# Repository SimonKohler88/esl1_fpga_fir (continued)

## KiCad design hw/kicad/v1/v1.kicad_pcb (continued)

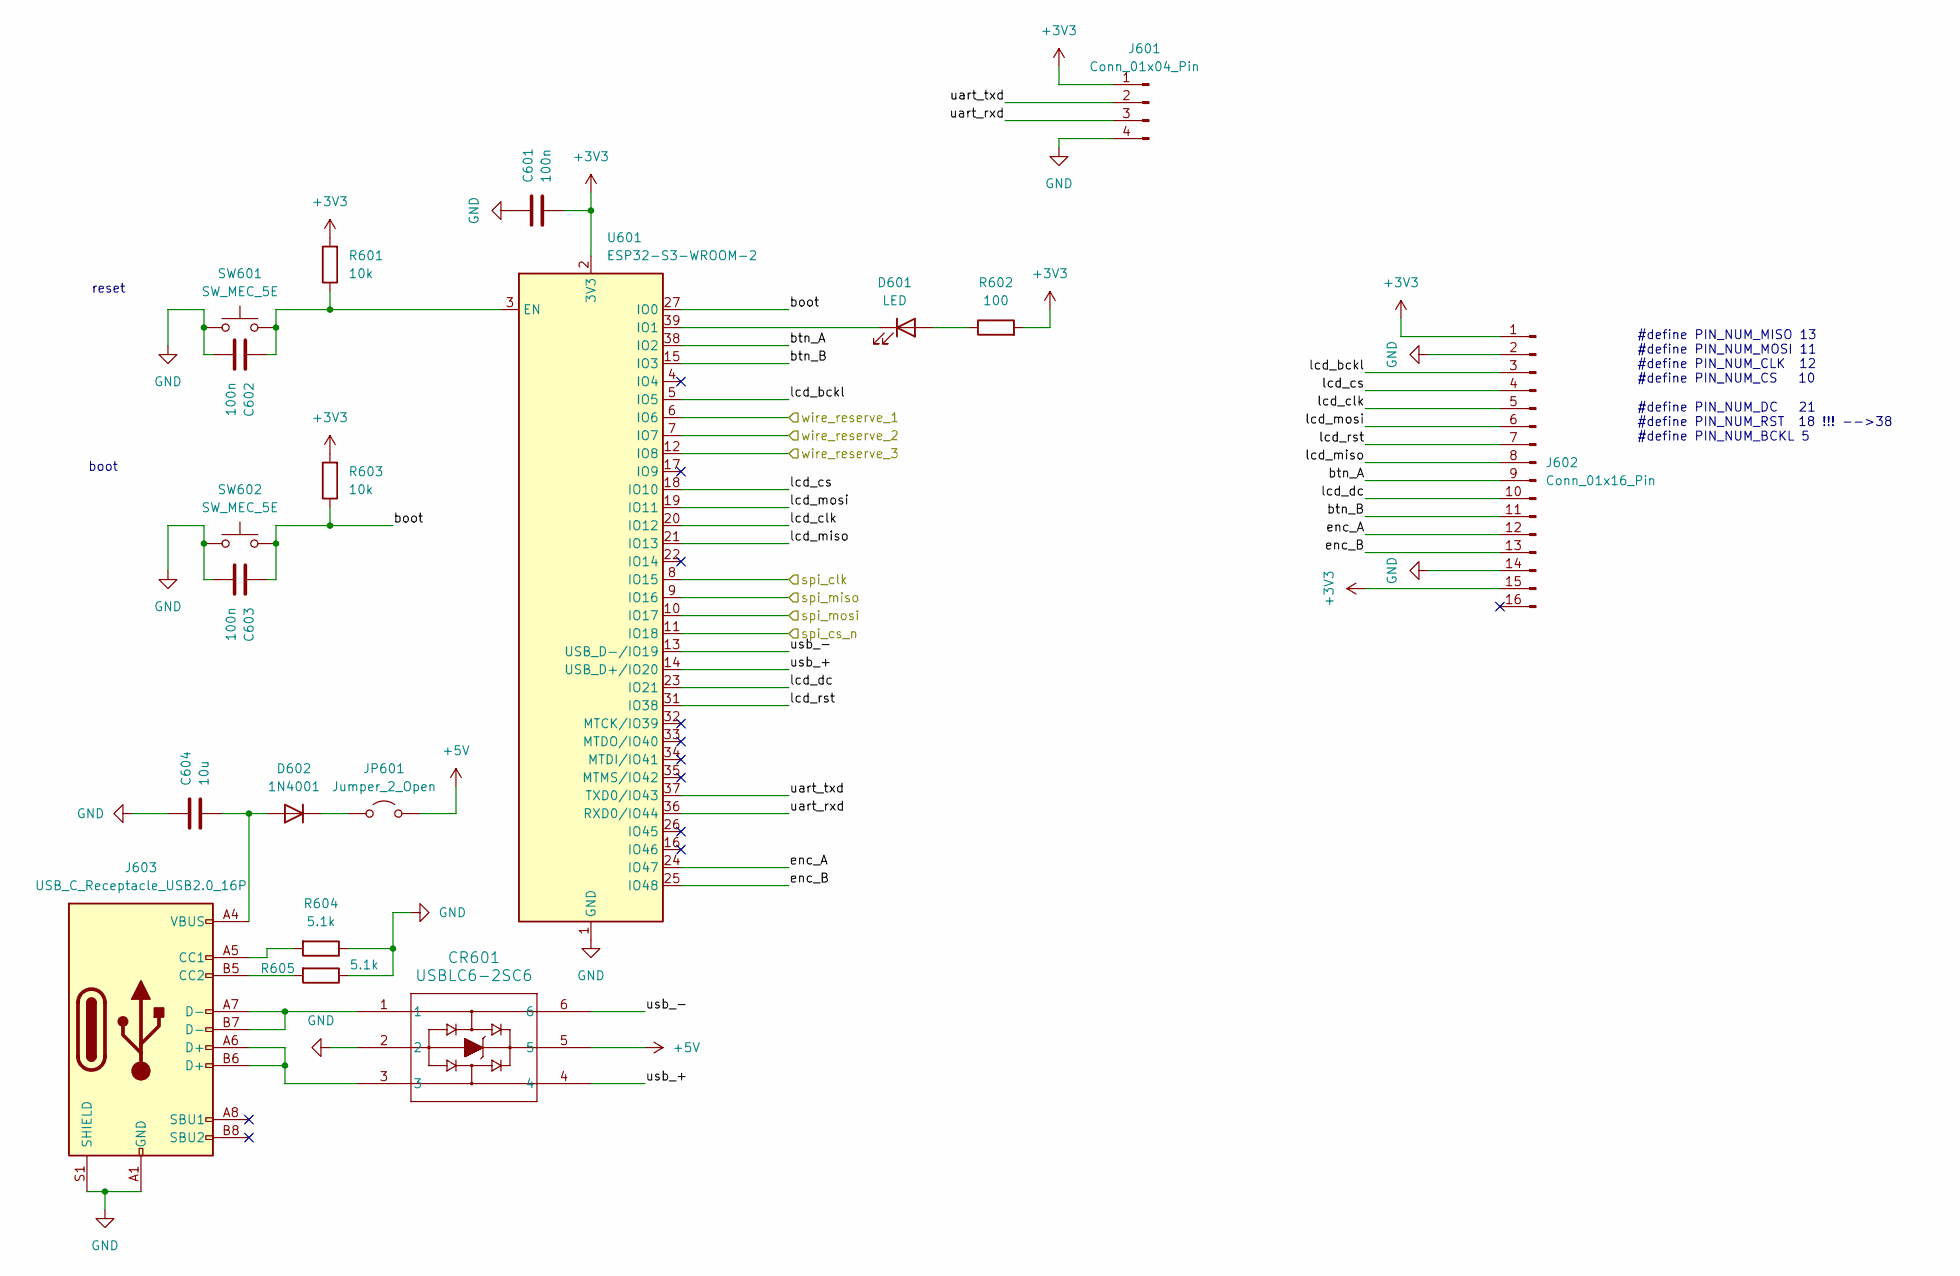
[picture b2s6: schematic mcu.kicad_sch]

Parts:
C601, C602, C603: 100n; C_1206_3216Metric_Pad1.33x1.80mm_HandSolder
C604: 10u; C_1206_3216Metric_Pad1.33x1.80mm_HandSolder
CR601: USBLC6-2SC6; SOT-23-6_Handsoldering
D601: LED; LED_1206_3216Metric_Pad1.42x1.75mm_HandSolder
D602: 1N4001; D_DO-41_SOD81_P10.16mm_Horizontal
J601: Conn_01x04_Pin; PinHeader_1x04_P2.54mm_Vertical
J602: Conn_01x16_Pin; PinHeader_2x08_P2.54mm_Vertical
J603: USB_C_Receptacle_USB2.0_16P; USB_C_Receptacle_GCT_USB4105-xx-A_16P_TopMnt_Horizontal
JP601: Jumper_2_Open; PinHeader_1x02_P2.54mm_Vertical
R601, R603: 10k; R_1206_3216Metric_Pad1.30x1.75mm_HandSolder
R602: 100; R_1206_3216Metric_Pad1.30x1.75mm_HandSolder
R604, R605: 5.1k; R_1206_3216Metric_Pad1.30x1.75mm_HandSolder
SW601, SW602: SW_MEC_5E; SW_Push_1P1T_NO_CK_KSC9xxJ
U601: ESP32-S3-WROOM-2

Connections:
+3V3: C601.2, J601.1, J602.1, J602.15, R601.2, R602.2, R603.2, U601.2 (3V3); also elsewhere on the board
+5V: CR601.5, JP601.2 (B); also elsewhere on the board
/DSV/spi_clk: U601.8 (IO15); also elsewhere on the board
/DSV/spi_cs_n: U601.11 (IO18); also elsewhere on the board
/DSV/spi_miso: U601.9 (IO16); also elsewhere on the board
/DSV/spi_mosi: U601.10 (IO17); also elsewhere on the board
/DSV/wire_reserve_1: U601.6 (IO6); also elsewhere on the board
/DSV/wire_reserve_2: U601.7 (IO7); also elsewhere on the board
/DSV/wire_reserve_3: U601.12 (IO8); also elsewhere on the board
/MCU/boot: C603.1, R603.1, SW602.2, U601.27 (IO0)
/MCU/btn_A: J602.9, U601.38 (IO2)
/MCU/btn_B: J602.11, U601.15 (IO3)
/MCU/enc_A: J602.12, U601.24 (IO47)
/MCU/enc_B: J602.13, U601.25 (IO48)
/MCU/lcd_bckl: J602.3, U601.5 (IO5)
/MCU/lcd_clk: J602.5, U601.20 (IO12)
/MCU/lcd_cs: J602.4, U601.18 (IO10)
/MCU/lcd_dc: J602.10, U601.23 (IO21)
/MCU/lcd_miso: J602.8, U601.21 (IO13)
/MCU/lcd_mosi: J602.6, U601.19 (IO11)
/MCU/lcd_rst: J602.7, U601.31 (IO38)
/MCU/uart_rxd: J601.3, U601.36 (RXD0/IO44)
/MCU/uart_txd: J601.2, U601.37 (TXD0/IO43)
/MCU/usb_+: CR601.4, U601.14 (USB_D+/IO20)
/MCU/usb_-: CR601.6, U601.13 (USB_D-/IO19)
GND: C601.1, C602.2, C603.2, C604.1, CR601.2, J601.4, J602.2, J602.14, J603.A1 (GND), J603.A12 (GND), J603.B1 (GND), J603.B12 (GND), J603.S1 (SHIELD), R604.1, R605.1, SW601.1, SW602.1, U601.1 (GND), U601.40 (GND), U601.41 (GND); also elsewhere on the board
unnamed: CR601.1, J603.A7 (D-), J603.B7 (D-)
unnamed: CR601.3, J603.A6 (D+), J603.B6 (D+)
unnamed: D601.2 (A), R602.1
unnamed: D601.1 (K), U601.39 (IO1)
unnamed: C604.2, D602.2 (A), J603.A4 (VBUS), J603.A9 (VBUS), J603.B4 (VBUS), J603.B9 (VBUS)
unnamed: D602.1 (K), JP601.1 (A)
unnamed: J603.A5 (CC1), R604.2
unnamed: J603.B5 (CC2), R605.2
unnamed: C602.1, R601.1, SW601.2, U601.3 (EN)

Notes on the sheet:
boot
reset
#define PIN_NUM_MISO 13 #define PIN_NUM_MOSI 11 #define PIN_NUM_CLK 12 #define PIN_NUM_CS 10 #define PIN_NUM_DC 21 #define PIN_NUM_RST 18 !!! -->38 #define PIN_NUM_BCKL 5

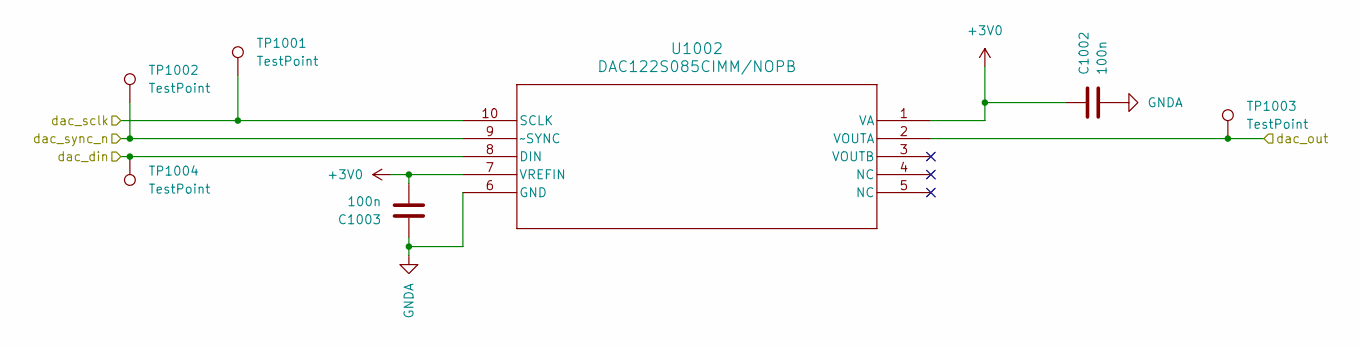
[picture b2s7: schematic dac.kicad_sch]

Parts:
C1002, C1003: 100n; C_1206_3216Metric_Pad1.33x1.80mm_HandSolder
TP1001, TP1002, TP1003, TP1004: TestPoint; TestPoint_Pad_D1.0mm
U1002: DAC122S085CIMM/NOPB; VSSOP-10_3x3mm_P0.5mm

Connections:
+3V0: C1002.1, C1003.2, U1002.1 (VA), U1002.7 (VREFIN); also elsewhere on the board
/Analog Output/DAC/dac_out: TP1003.1, U1002.2 (VOUTA); also elsewhere on the board
/Analog Output/dac_din: TP1004.1, U1002.8 (DIN); also elsewhere on the board
/Analog Output/dac_sclk: TP1001.1, U1002.10 (SCLK); also elsewhere on the board
/Analog Output/dac_sync_n: TP1002.1, U1002.9 (~SYNC); also elsewhere on the board
GND: C1002.2, C1003.1, U1002.6 (GND); also elsewhere on the board

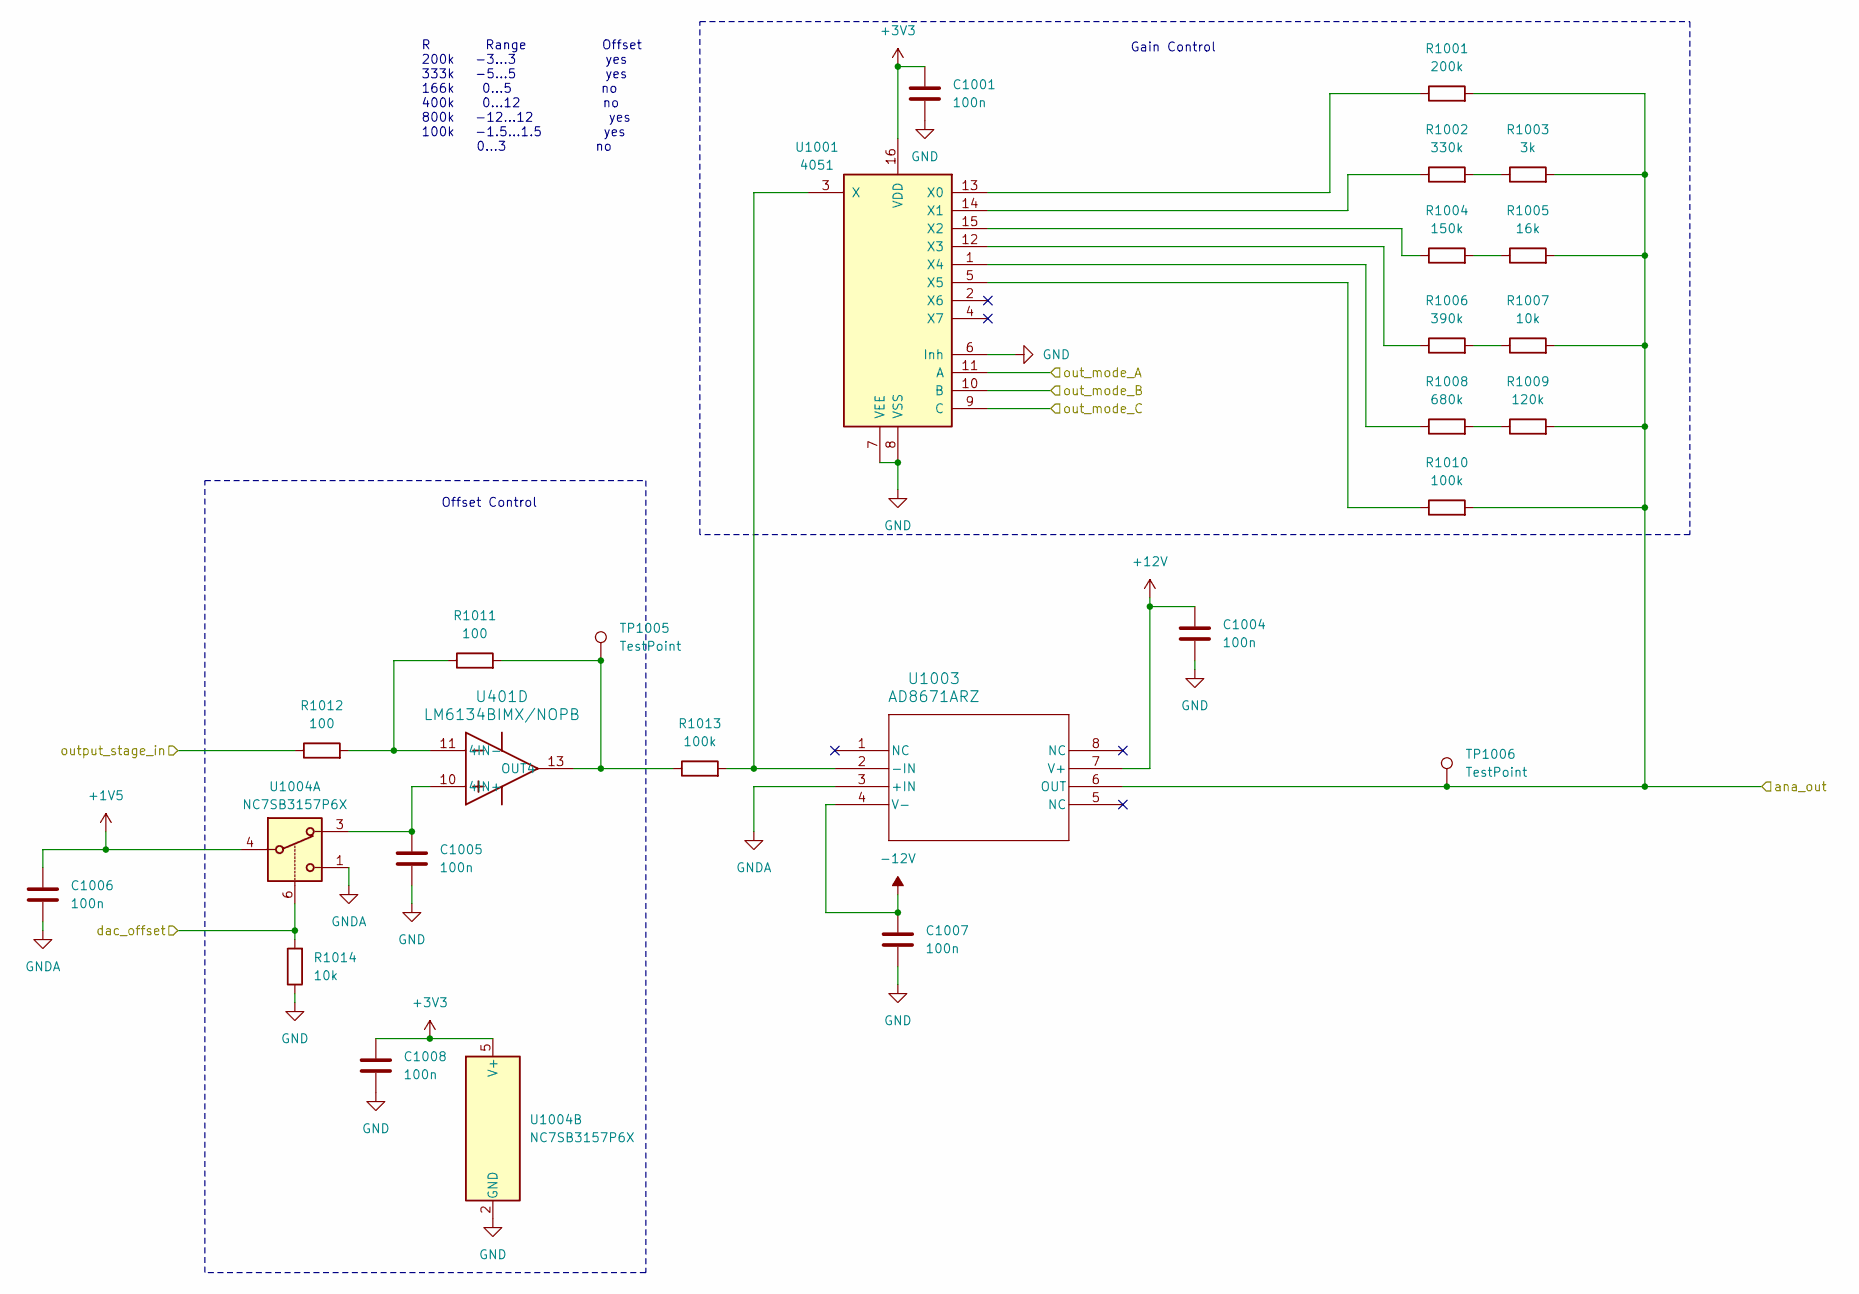
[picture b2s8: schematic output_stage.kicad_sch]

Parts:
C1001, C1004, C1005, C1007, C1008: 100n; C_1206_3216Metric_Pad1.33x1.80mm_HandSolder
C1006: 100n; C_0603_1608Metric_Pad1.08x0.95mm_HandSolder
R1001: 200k; R_1206_3216Metric_Pad1.30x1.75mm_HandSolder
R1002: 330k; R_1206_3216Metric_Pad1.30x1.75mm_HandSolder
R1003: 3k; R_1206_3216Metric_Pad1.30x1.75mm_HandSolder
R1004: 150k; R_1206_3216Metric_Pad1.30x1.75mm_HandSolder
R1005: 16k; R_1206_3216Metric_Pad1.30x1.75mm_HandSolder
R1006: 390k; R_1206_3216Metric_Pad1.30x1.75mm_HandSolder
R1007, R1014: 10k; R_1206_3216Metric_Pad1.30x1.75mm_HandSolder
R1008: 680k; R_1206_3216Metric_Pad1.30x1.75mm_HandSolder
R1009: 120k; R_1206_3216Metric_Pad1.30x1.75mm_HandSolder
R1010, R1013: 100k; R_1206_3216Metric_Pad1.30x1.75mm_HandSolder
R1011, R1012: 100; R_1206_3216Metric_Pad1.30x1.75mm_HandSolder
TP1005, TP1006: TestPoint; TestPoint_Pad_D1.0mm
U401: LM6134BIMX/NOPB; SOIC-14_3.9x8.7mm_P1.27mm
U1001: 4051; SOIC-16_3.9x9.9mm_P1.27mm
U1003: AD8671ARZ; R_8_ADI
U1004: NC7SB3157P6X; SOT-363_SC-70-6

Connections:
+1V5: C1006.1, U1004.4; also elsewhere on the board
+3V3: C1001.1, C1008.1, U1001.16 (VDD), U1004.5 (V+); also elsewhere on the board
+12V: C1004.1, U1003.7 (V+); also elsewhere on the board
-12V: C1007.1, U1003.4 (V-); also elsewhere on the board
/Analog Output/Output Stage/output_stage_in: R1012.1; also elsewhere on the board
/Analog Output/ana_out: R1001.2, R1003.2, R1005.2, R1007.2, R1009.2, R1010.2, TP1006.1, U1003.6 (OUT); also elsewhere on the board
/Analog Output/dac_offset: R1014.2, U1004.6; also elsewhere on the board
/Analog Output/out_mode_A: U1001.11 (A); also elsewhere on the board
/Analog Output/out_mode_B: U1001.10 (B); also elsewhere on the board
/Analog Output/out_mode_C: U1001.9 (C); also elsewhere on the board
GND: C1001.2, C1004.2, C1005.2, C1006.2, C1007.2, C1008.2, R1014.1, U1001.6 (Inh), U1001.7 (VEE), U1001.8 (VSS), U1003.3 (+IN), U1004.1, U1004.2 (GND); also elsewhere on the board
unnamed: R1002.2, R1003.1
unnamed: R1004.2, R1005.1
unnamed: R1006.2, R1007.1
unnamed: R1008.2, R1009.1
unnamed: C1005.1, U401.10 (4IN+), U1004.3
unnamed: R1011.1, R1012.2, U401.11 (4IN-)
unnamed: R1011.2, R1013.1, TP1005.1, U401.13 (OUT4)
unnamed: R1001.1, U1001.13 (X0)
unnamed: R1002.1, U1001.14 (X1)
unnamed: R1004.1, U1001.15 (X2)
unnamed: R1006.1, U1001.12 (X3)
unnamed: R1008.1, U1001.1 (X4)
unnamed: R1010.1, U1001.5 (X5)
unnamed: R1013.2, U1001.3 (X), U1003.2 (-IN)

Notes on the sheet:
R Range Offset 200k -3...3 yes 333k -5...5 yes 166k 0...5 no 400k 0...12 no 800k -12...12 yes 100k -1.5...1.5 yes 0...3 no
Offset Control
Gain Control

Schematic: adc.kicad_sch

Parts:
C901: 100n; C_1206_3216Metric_Pad1.33x1.80mm_HandSolder
C902: 3.3u; C_1206_3216Metric_Pad1.33x1.80mm_HandSolder
C903: 470p; C_0603_1608Metric_Pad1.08x0.95mm_HandSolder
D901, D902: BZV55B3V3; D_MiniMELF
R901: 100; R_1206_3216Metric_Pad1.30x1.75mm_HandSolder
TP901, TP902, TP903, TP904: TestPoint; TestPoint_Pad_D1.0mm
U901: TLV9022DR; SOIC-8_3.9x4.9mm_P1.27mm
U902: ADS7883SBDBVT; SOT-23-6_Handsoldering

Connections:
+3V0: C902.2, U902.1 (VDD); also elsewhere on the board
+3V3: C901.1, D901.1 (K), U901.3 (IN1+), U901.8 (VCC); also elsewhere on the board
/DSV/adc_cs_n: TP903.1, U902.6 (CS_N); also elsewhere on the board
/DSV/adc_sclk: TP901.1, U902.4 (SCLK); also elsewhere on the board
/DSV/adc_sdo: TP902.1, U902.5 (SDO); also elsewhere on the board
/DSV/clip_high_out: U901.1 (OUT1); also elsewhere on the board
/DSV/clip_low_out: U901.7 (OUT2); also elsewhere on the board
/analog Input/ADC/adc_in: R901.1; also elsewhere on the board
GND: C901.2, C902.1, C903.2, D902.2 (A), U901.4 (GND), U901.6 (IN2-), U902.2 (GND); also elsewhere on the board
unnamed: C903.1, D901.2 (A), D902.1 (K), R901.2, TP904.1, U901.2 (IN1-), U901.5 (IN2+), U902.3 (VIN)

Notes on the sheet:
ADC protection
clipping detection

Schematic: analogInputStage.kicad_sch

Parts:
C701, C702, C703, C704, C706: 100n; C_1206_3216Metric_Pad1.33x1.80mm_HandSolder
C705: 100n; C_0603_1608Metric_Pad1.08x0.95mm_HandSolder
D701, D702: BZV55B12; D_MiniMELF
R701: 47k; R_1206_3216Metric_Pad1.30x1.75mm_HandSolder
R702, R704, R709: 2k7; R_1206_3216Metric_Pad1.30x1.75mm_HandSolder
R703: 27k; R_1206_3216Metric_Pad1.30x1.75mm_HandSolder
R705: 56k; R_1206_3216Metric_Pad1.30x1.75mm_HandSolder
R706: 3k6; R_1206_3216Metric_Pad1.30x1.75mm_HandSolder
R707: 160; R_1206_3216Metric_Pad1.30x1.75mm_HandSolder
R708: 22k; R_1206_3216Metric_Pad1.30x1.75mm_HandSolder
R710: 11k; R_1206_3216Metric_Pad1.30x1.75mm_HandSolder
R711: 240; R_1206_3216Metric_Pad1.30x1.75mm_HandSolder
R712: 91k; R_1206_3216Metric_Pad1.30x1.75mm_HandSolder
R713: 8k2; R_1206_3216Metric_Pad1.30x1.75mm_HandSolder
R714: 560; R_1206_3216Metric_Pad1.30x1.75mm_HandSolder
R715, R717: 100; R_1206_3216Metric_Pad1.30x1.75mm_HandSolder
R716: 100k; R_1206_3216Metric_Pad1.30x1.75mm_HandSolder
R718: 10k; R_1206_3216Metric_Pad1.30x1.75mm_HandSolder
TP701, TP702, TP703: TestPoint; TestPoint_Pad_D1.0mm
U301: LM6134BIMX/NOPB; SOIC-14_3.9x8.7mm_P1.27mm
U701: 4051; SOIC-16_3.9x9.9mm_P1.27mm
U702: NC7SB3157P6X; SOT-363_SC-70-6
U703: AD8671ARZ; R_8_ADI

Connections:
+1V5: C705.1, U702.4; also elsewhere on the board
+3V3: C701.1, C702.1, U701.16 (VDD), U702.5 (V+); also elsewhere on the board
+12V: C703.1, D701.1 (K), U703.7 (V+); also elsewhere on the board
-12V: C706.1, D702.2 (A), U703.4 (V-); also elsewhere on the board
/DSV/adc_offset: R718.2, U702.6; also elsewhere on the board
/DSV/inp_mode_A: U701.11 (A); also elsewhere on the board
/DSV/inp_mode_B: U701.10 (B); also elsewhere on the board
/DSV/inp_mode_C: U701.9 (C); also elsewhere on the board
/analog Input/ana_in: D701.2 (A), D702.1 (K), R716.1, TP701.1; also elsewhere on the board
/analog Input/analog input stage/input_stage_out: R715.2, TP703.1, U301.2 (OUT1); also elsewhere on the board
GND: C701.2, C702.2, C703.2, C704.2, C705.2, C706.2, R718.1, U701.6 (Inh), U701.7 (VEE), U701.8 (VSS), U702.1, U702.2 (GND), U703.3 (+IN); also elsewhere on the board
unnamed: R701.2, R702.1
unnamed: R703.2, R704.1
unnamed: R705.2, R706.1
unnamed: R706.2, R707.1
unnamed: R708.2, R709.1
unnamed: R710.2, R711.1
unnamed: R712.2, R713.1
unnamed: R713.2, R714.1
unnamed: C704.1, U301.5 (1IN+), U702.3
unnamed: R715.1, R717.2, U301.4 (1IN-)
unnamed: R701.1, U701.13 (X0)
unnamed: R703.1, U701.14 (X1)
unnamed: R705.1, U701.15 (X2)
unnamed: R708.1, U701.12 (X3)
unnamed: R710.1, U701.1 (X4)
unnamed: R712.1, U701.5 (X5)
unnamed: R716.2, U701.3 (X), U703.2 (-IN)
unnamed: R702.2, R704.2, R707.2, R709.2, R711.2, R714.2, R717.1, TP702.1, U703.6 (OUT)

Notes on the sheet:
R Range Offset 50k0 -3...3 yes 30k0 -5...5 yes 60k 0...5 no 25k 0...12 no 12k5 -12...12 yes 100k -1.5...1.5 yes 0...3 no
Gain Control
Offset Control

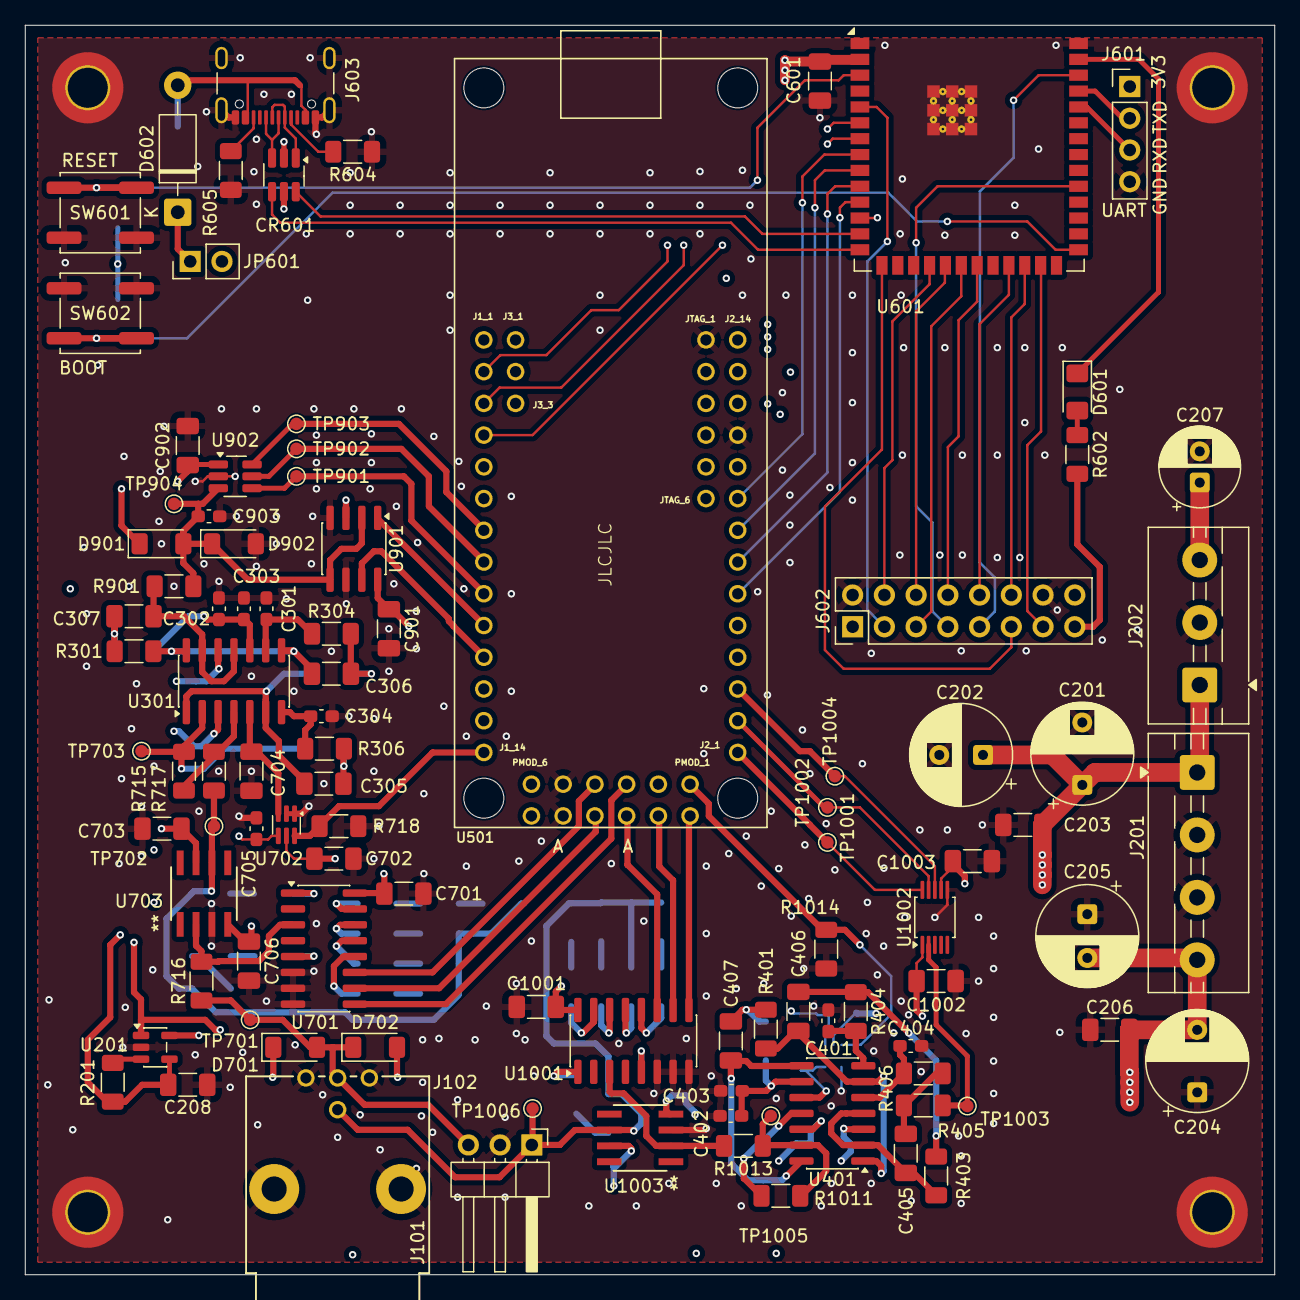
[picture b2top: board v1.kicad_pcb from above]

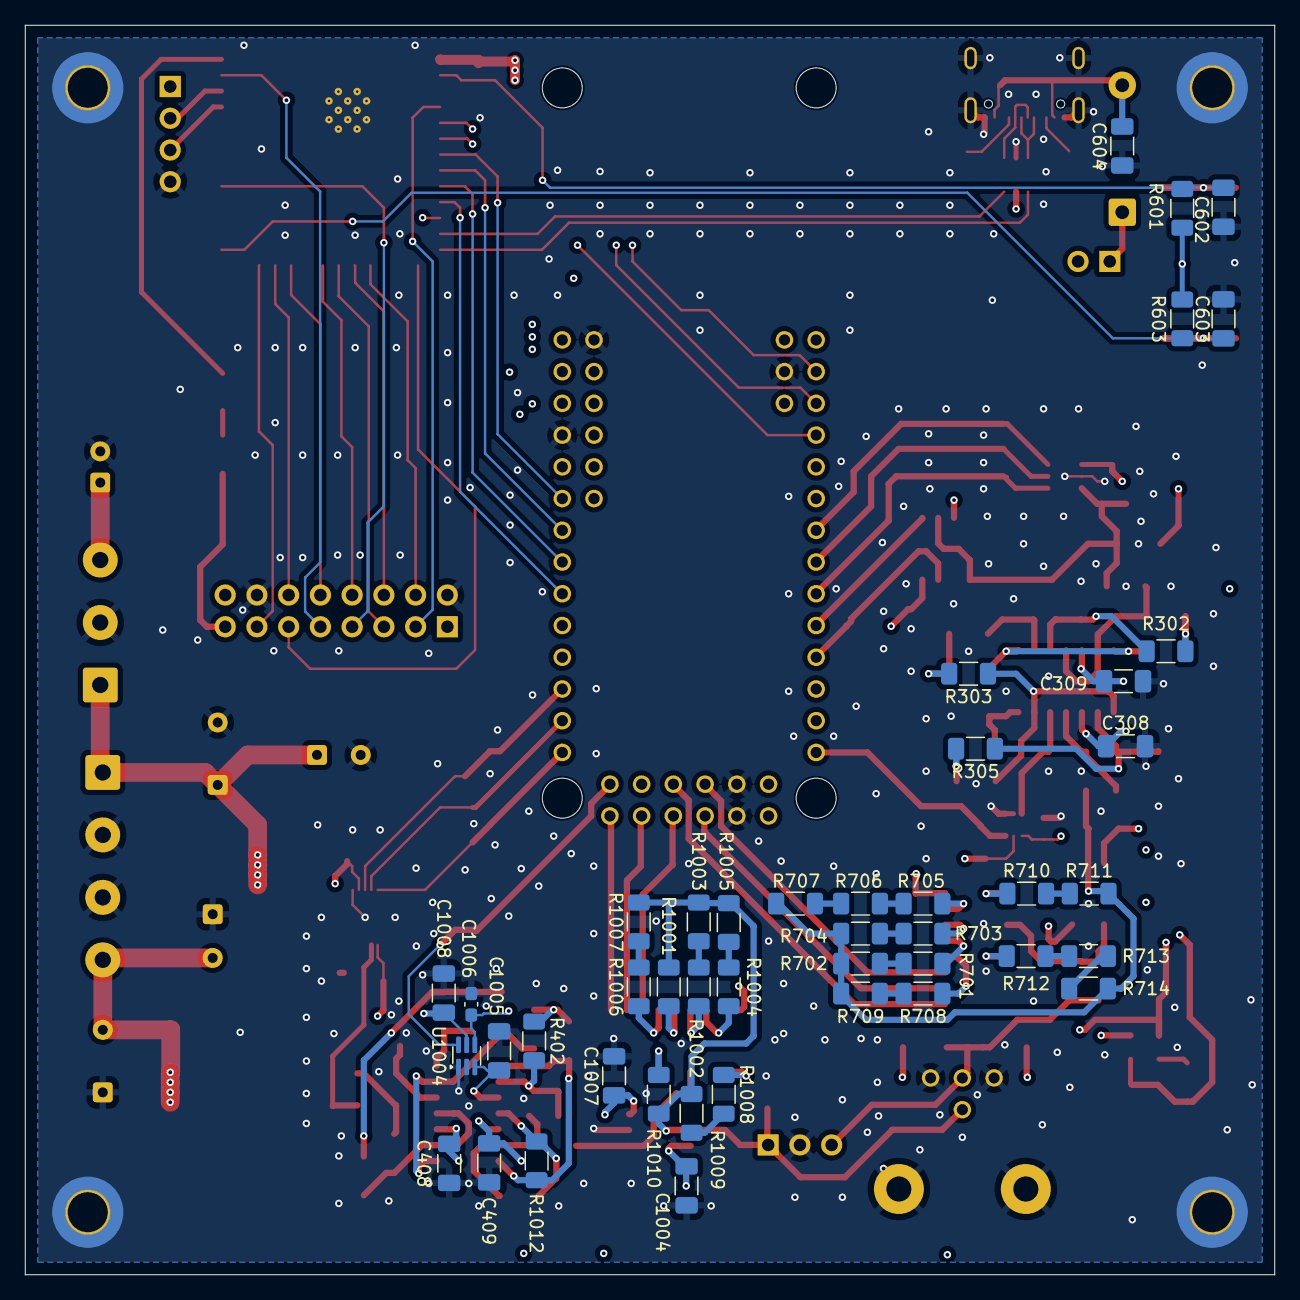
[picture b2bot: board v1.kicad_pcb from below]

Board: 4 copper layers, 100.0 x 100.0 mm, 146 parts (44 on the bottom side), 111 nets.

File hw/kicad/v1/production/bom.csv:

Designator,Footprint,Quantity,Value,LCSC Part #
"C1001, C1002, C1003, C1004, C1005, C1007, C1008, C203, C206, C208, C308, C309, C408, C409, C601, C602, C603, C701, C702, C703, C704, C706, C901",1206,23,100n,
"C1006, C705",0603,2,100n,
"C201, C204",CP_Radial_D8.0mm_P5.00mm,2,680u,
"C202, C205",CP_Radial_D8.0mm_P3.50mm,2,100u,
C207,CP_Radial_D6.3mm_P2.50mm,1,10u,
"C301, C302, C401, C402, C903",0603,5,470p,
"C303, C403",0603,2,330p,
"C304, C404",0603,2,68p,
"C305, C306, C307, C405, C406, C407",1206,6,1n,
C604,1206,1,10u,
C902,1206,1,3.3u,
CR601,SOT-23-6_Handsoldering,1,USBLC6-2SC6,
D601,1206,1,LED,
D602,D_DO-41_SOD81_P10.16mm_Horizontal,1,1N4001,
"D701, D702",D_MiniMELF,2,BZV55B12,
"D901, D902",D_MiniMELF,2,BZV55B3V3,
J101,PinHeader_1x03_P2.54mm_Horizontal,1,Conn_01x03_Pin,
J102,CONN_6575_AMP,1,031-6575,
J201,TerminalBlock_MaiXu_MX126-5.0-04P_1x04_P5.00mm,1,Screw_Terminal_01x04,
J202,TerminalBlock_MaiXu_MX126-5.0-03P_1x03_P5.00mm,1,Screw_Terminal_01x03,
J601,PinHeader_1x04_P2.54mm_Vertical,1,Conn_01x04_Pin,
J602,PinHeader_2x08_P2.54mm_Vertical,1,Conn_01x16_Pin,
J603,USB_C_Receptacle_GCT_USB4105-xx-A_16P_TopMnt_Horizontal,1,USB_C_Receptacle_USB2.0_16P,
JP601,PinHeader_1x02_P2.54mm_Vertical,1,Jumper_2_Open,
R1001,1206,1,200k,
R1002,1206,1,330k,
R1003,1206,1,3k,
R1004,1206,1,150k,
R1005,1206,1,16k,
R1006,1206,1,390k,
"R1007, R1014, R201, R601, R603, R718",1206,6,10k,
R1008,1206,1,680k,
R1009,1206,1,120k,
"R1010, R1013, R716",1206,3,100k,
"R1011, R1012, R602, R715, R717, R901",1206,6,100,
"R301, R401",1206,2,120,
"R302, R402, R711",1206,3,240,
"R303, R403, R707",1206,3,160,
"R304, R404",1206,2,360,
"R305, R405",1206,2,470,
"R306, R406",1206,2,820,
"R604, R605",1206,2,5.1k,
R701,1206,1,47k,
"R702, R704, R709",1206,3,2k7,
R703,1206,1,27k,
R705,1206,1,56k,
R706,1206,1,3k6,
R708,1206,1,22k,
R710,1206,1,11k,
R712,1206,1,91k,
R713,1206,1,8k2,
R714,1206,1,560,
"SW601, SW602",SW_Push_1P1T_NO_CK_KSC9xxJ,2,SW_MEC_5E,
"TP1001, TP1002, TP1003, TP1004, TP1005, TP1006, TP701, TP702, TP703, TP901, TP902, TP903, TP904",TestPoint_Pad_D1.0mm,13,TestPoint,
"U1001, U701",SOIC-16_3.9x9.9mm_P1.27mm,2,4051,
U1002,VSSOP-10_3x3mm_P0.5mm,1,DAC122S085CIMM/NOPB,
"U1003, U703",R_8_ADI,2,AD8671ARZ,
"U1004, U702",SOT-363_SC-70-6,2,NC7SB3157P6X,
U201,SOT-23-5,1,REF2030,
"U301, U401",SOIC-14_3.9x8.7mm_P1.27mm,2,LM6134BIMX/NOPB,
U501,MAX1000,1,MAX1000,
U601,ESP32-S3-WROOM-2,1,ESP32-S3-WROOM-2,
U901,SOIC-8_3.9x4.9mm_P1.27mm,1,TLV9022DR,
U902,SOT-23-6_Handsoldering,1,ADS7883SBDBVT,

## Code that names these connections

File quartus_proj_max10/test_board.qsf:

# -------------------------------------------------------------------------- #
#
# Copyright (C) 2024  Intel Corporation. All rights reserved.
# Your use of Intel Corporation's design tools, logic functions 
# and other software and tools, and any partner logic 
# functions, and any output files from any of the foregoing 
# (including device programming or simulation files), and any 
# associated documentation or information are expressly subject 
# to the terms and conditions of the Intel Program License 
# Subscription Agreement, the Intel Quartus Prime License Agreement,
# the Intel FPGA IP License Agreement, or other applicable license
# agreement, including, without limitation, that your use is for
# the sole purpose of programming logic devices manufactured by
# Intel and sold by Intel or its authorized distributors.  Please
# refer to the applicable agreement for further details, at
# https://fpgasoftware.intel.com/eula.
#
# -------------------------------------------------------------------------- #
#
# Quartus Prime
# Version 23.1std.1 Build 993 05/14/2024 SC Lite Edition
# Date created = 09:23:21  July 30, 2025
#
# -------------------------------------------------------------------------- #
#
# Notes:
#
# 1) The default values for assignments are stored in the file:
#		test_board_assignment_defaults.qdf
#    If this file doesn't exist, see file:
#		assignment_defaults.qdf
#
# 2) Intel recommends that you do not modify this file. This
#    file is updated automatically by the Quartus Prime software
#    and any changes you make may be lost or overwritten.
#
# -------------------------------------------------------------------------- #


set_global_assignment -name FAMILY "MAX 10"
set_global_assignment -name DEVICE 10M08SAU169C8G
set_global_assignment -name TOP_LEVEL_ENTITY test_board
set_global_assignment -name ORIGINAL_QUARTUS_VERSION 18.1.0
set_global_assignment -name PROJECT_CREATION_TIME_DATE "11:47:22  MARCH 18, 2019"
set_global_assignment -name LAST_QUARTUS_VERSION "20.1.1 Lite Edition"
set_global_assignment -name PROJECT_OUTPUT_DIRECTORY output_files
set_global_assignment -name DEVICE_FILTER_PACKAGE UFBGA
set_global_assignment -name ERROR_CHECK_FREQUENCY_DIVISOR 256
set_global_assignment -name ENABLE_OCT_DONE OFF
set_global_assignment -name USE_CONFIGURATION_DEVICE OFF
set_global_assignment -name CRC_ERROR_OPEN_DRAIN OFF
set_global_assignment -name STRATIX_DEVICE_IO_STANDARD "3.3-V LVTTL"
set_global_assignment -name PROJECT_IP_REGENERATION_POLICY ALWAYS_REGENERATE_IP
set_global_assignment -name POWER_PRESET_COOLING_SOLUTION "23 MM HEAT SINK WITH 200 LFPM AIRFLOW"
set_global_assignment -name POWER_BOARD_THERMAL_MODEL "NONE (CONSERVATIVE)"
set_global_assignment -name FLOW_ENABLE_POWER_ANALYZER ON
set_global_assignment -name POWER_DEFAULT_INPUT_IO_TOGGLE_RATE "12.5 %"
set_global_assignment -name EXTERNAL_FLASH_FALLBACK_ADDRESS 00000000
set_global_assignment -name INTERNAL_FLASH_UPDATE_MODE "SINGLE IMAGE WITH ERAM"
set_global_assignment -name ENABLE_DEVICE_WIDE_RESET OFF
set_global_assignment -name ENABLE_CONFIGURATION_PINS OFF
set_global_assignment -name PARTITION_NETLIST_TYPE SOURCE -section_id Top
set_global_assignment -name PARTITION_FITTER_PRESERVATION_LEVEL PLACEMENT_AND_ROUTING -section_id Top
set_global_assignment -name PARTITION_COLOR 16764057 -section_id Top
set_global_assignment -name OUTPUT_IO_TIMING_NEAR_END_VMEAS "HALF VCCIO" -rise
set_global_assignment -name OUTPUT_IO_TIMING_NEAR_END_VMEAS "HALF VCCIO" -fall
set_global_assignment -name OUTPUT_IO_TIMING_FAR_END_VMEAS "HALF SIGNAL SWING" -rise
set_global_assignment -name OUTPUT_IO_TIMING_FAR_END_VMEAS "HALF SIGNAL SWING" -fall
set_location_assignment PIN_A12 -to DQ[15]
set_location_assignment PIN_B13 -to DQ[14]
set_location_assignment PIN_B12 -to DQ[13]
set_location_assignment PIN_C12 -to DQ[12]
set_location_assignment PIN_D12 -to DQ[11]
set_location_assignment PIN_E13 -to DQ[10]
set_location_assignment PIN_E12 -to DQ[9]
set_location_assignment PIN_F13 -to DQ[8]
set_location_assignment PIN_F8 -to DQ[7]
set_location_assignment PIN_G9 -to DQ[6]
set_location_assignment PIN_D9 -to DQ[5]
set_location_assignment PIN_E10 -to DQ[4]
set_location_assignment PIN_F9 -to DQ[3]
set_location_assignment PIN_F10 -to DQ[2]
set_location_assignment PIN_G10 -to DQ[1]
set_location_assignment PIN_D11 -to DQ[0]
set_location_assignment PIN_M10 -to A[11]
set_location_assignment PIN_N4 -to A[10]
set_location_assignment PIN_N8 -to A[9]
set_location_assignment PIN_M13 -to A[8]
set_location_assignment PIN_L10 -to A[7]
set_location_assignment PIN_N9 -to A[6]
set_location_assignment PIN_M11 -to A[5]
set_location_assignment PIN_N10 -to A[4]
set_location_assignment PIN_J8 -to A[3]
set_location_assignment PIN_N5 -to A[2]
set_location_assignment PIN_M5 -to A[1]
set_location_assignment PIN_K6 -to A[0]
set_location_assignment PIN_H6 -to CLK12M
set_location_assignment PIN_F12 -to DQM[1]
set_location_assignment PIN_E9 -to DQM[0]
set_location_assignment PIN_K8 -to BA[1]
set_location_assignment PIN_N6 -to BA[0]
set_location_assignment PIN_M7 -to RAS
set_location_assignment PIN_E7 -to RESET
set_location_assignment PIN_M9 -to CLK
set_location_assignment PIN_M8 -to CKE
set_location_assignment PIN_N7 -to CAS
set_location_assignment PIN_K7 -to WE
set_location_assignment PIN_M4 -to CS
set_location_assignment PIN_E6 -to USER_BTN
set_location_assignment PIN_J6 -to SEN_SPC
set_location_assignment PIN_K5 -to SEN_SDO
set_location_assignment PIN_J7 -to SEN_SDI
set_location_assignment PIN_L5 -to SEN_CS
set_location_assignment PIN_B2 -to F_DO
set_location_assignment PIN_A2 -to F_DI
set_location_assignment PIN_B3 -to F_CS
set_location_assignment PIN_A3 -to F_CLK
set_location_assignment PIN_A4 -to BDBUS0
set_location_assignment PIN_B4 -to BDBUS1
set_location_assignment PIN_A8 -to LED0
set_location_assignment PIN_A9 -to LED1
set_location_assignment PIN_A11 -to LED2
set_location_assignment PIN_A10 -to LED3
set_location_assignment PIN_B10 -to LED4
set_location_assignment PIN_C9 -to LED5
set_location_assignment PIN_C10 -to LED6
set_location_assignment PIN_D8 -to LED7
set_location_assignment PIN_C4 -to NSTATUS
set_location_assignment PIN_B9 -to DEVCLRn
set_location_assignment PIN_M3 -to DAC_OFFSET
set_location_assignment PIN_F1 -to ADC_SPI_CS_N
set_location_assignment PIN_J2 -to ADC_OFFSET
set_location_assignment PIN_K10 -to CLIP_H
set_location_assignment PIN_H5 -to CLIP_L
set_global_assignment -name MIN_CORE_JUNCTION_TEMP 0
set_global_assignment -name MAX_CORE_JUNCTION_TEMP 85
set_location_assignment PIN_M1 -to IN_MUX[0]
set_location_assignment PIN_M2 -to IN_MUX[2]
set_location_assignment PIN_K1 -to IN_MUX[1]
set_location_assignment PIN_K2 -to OUT_MUX[0]
set_location_assignment PIN_N2 -to OUT_MUX[1]
set_location_assignment PIN_N3 -to OUT_MUX[2]
set_location_assignment PIN_E4 -to ADC_SPI_DATA_IN
set_location_assignment PIN_H8 -to ADC_SPI_CLK
set_location_assignment PIN_L12 -to DAC_SPI_CLK
set_location_assignment PIN_J12 -to DAC_SPI_CS_N
set_location_assignment PIN_J13 -to DAC_SPI_DATA
set_location_assignment PIN_G12 -to SPI_CLK
set_location_assignment PIN_J10 -to SPI_CS_N
set_location_assignment PIN_H13 -to SPI_MISO
set_location_assignment PIN_H10 -to SPI_MOSI
set_global_assignment -name VHDL_INPUT_VERSION VHDL_2008
set_global_assignment -name VHDL_SHOW_LMF_MAPPING_MESSAGES OFF
set_location_assignment PIN_E1 -to RESERVE_1
set_location_assignment PIN_C2 -to RESERVE_2
set_location_assignment PIN_C1 -to RESERVE_3
set_global_assignment -name VHDL_FILE hdl/BUS_BYPASS_MUX/BUS_BYPASS_MUX.vhdl
set_global_assignment -name VHDL_FILE hdl/MCU_SPI/spi_reg_bank.vhdl
set_global_assignment -name VHDL_FILE hdl/MCU_SPI/spi_protocol.vhdl
set_global_assignment -name VHDL_FILE hdl/MCU_SPI/spi_phy.vhdl
set_global_assignment -name VHDL_FILE hdl/MCU_SPI/spi_cmd_package.vhdl
set_global_assignment -name VHDL_FILE hdl/MCU_SPI/MCU_SPI.vhdl
set_global_assignment -name VHDL_FILE hdl/DAC_SPI/DAC_SPI.vhdl
set_global_assignment -name VHDL_FILE hdl/FIR/fir_types.vhdl
set_global_assignment -name VHDL_FILE hdl/FIR/fir_filter.vhdl
set_global_assignment -name VHDL_FILE hdl/shift_reg_seq.vhd
set_global_assignment -name VHDL_FILE hdl/pwm_seq.vhd
set_global_assignment -name VHDL_FILE hdl/knightrider.vhd
set_global_assignment -name VHDL_FILE hdl/control_mux.vhd
set_global_assignment -name VHDL_FILE hdl/case_state_seq.vhd
set_global_assignment -name QIP_FILE ddrclk.qip
set_global_assignment -name SDC_FILE test_board.out.sdc
set_global_assignment -name BDF_FILE test_board.bdf
set_global_assignment -name QIP_FILE ip/pll_megafunc/pll.qip
set_global_assignment -name VHDL_FILE "d:\\GitHub\\esl1_fpga_fir\\quartus_proj_max10\\hdl\\ADC_SPI\\ADC_SPI.vhdl"
set_global_assignment -name VHDL_FILE "d:\\GitHub\\esl1_fpga_fir\\quartus_proj_max10\\hdl\\FIR\\fir_filter_tb.vhdl"
set_instance_assignment -name PARTITION_HIERARCHY root_partition -to | -section_id Top

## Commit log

2025-11-02 Codec Files Pichler
    Codec Files Pichler
2025-11-02 base project and nios for uart
2025-11-02 working nios with uart over jtag, leds over AV MM
2025-11-09 timer isr, jtag isr, console working wy better
2025-11-09 working with jtag_uart
2025-11-09 Erster Entwurf FIR Filter Thomas
2025-11-09 we leave it at jtag_uart
2025-11-09 CODEC related files and wrapper added
    CODEC related files provided by Prof. Pichler:
    codec_i2c_config.vhd, codec_i2c_ctrl.vhd, codec_i2c_top_struct.vhd, codec_if.vhd, ime_vga_audio_pll.vhd and ime_vga_audio_pll_002.v.
    Wrapper (Avalon compatible) and Testbench for our Project:
    codec_top.vhd, codec_top_tb_vhd
2025-11-09 implemented IOS for Audio, interface to fir filter
2025-11-09 Erstelle cmake um in Clion automatisch die Testbenches zu erstellen und zu simulieren.
2025-11-09 preload a standard set of filter coefficients at startup
2025-11-10 CMakeLists.txt verbessert, dass gtkwave gleich nach der Simulation startet
2025-11-10 compile in Const register for preload FIR Koeff
2025-11-10 Now with 50MHz Avalon Streaming Handshake
    Now with 50MHz Avalon Streaming Handshake
2025-11-10 Umsetzung Filter zum Zweiten
2025-11-10 Now with 50MHz Avalon Streaming Handshake
2025-11-10 interface prog
2025-11-11 fixed Address issue
2025-11-11 switch to normal uart
2025-11-11 change to use normal uart
2025-11-11 REALLY corrected Address issue
2025-11-17 Bilder Init für Dok
2025-11-17 Doku: Jupyter
2025-11-17 Added filter computation and write
    The 64 filter coefficients can be computed and written to the FPGA by defining the cutoff frequency(s) and filter type.
2025-11-18 commit fpga binaries
2025-12-01 Python Plots für Doku
    Python Plots für Doku
2025-12-01 Blockdiagramme etc. für Doku
    Blockdiagramme etc. für Doku
2025-12-01 dependency diagram teros
    dependency diagram teros
2025-12-01 3kHz plots
    3kHz plots
2026-02-25 kicad layout, max10 prj
2026-02-25 add dac interface, cleanup led stuff
2026-02-27 adding mcu spi interface, fir bypass mux
2026-02-28 Add status clear on read, Add Clip High and Clip low signals to status
2026-03-01 add basic esp32 project
2026-03-26 production gerber files
